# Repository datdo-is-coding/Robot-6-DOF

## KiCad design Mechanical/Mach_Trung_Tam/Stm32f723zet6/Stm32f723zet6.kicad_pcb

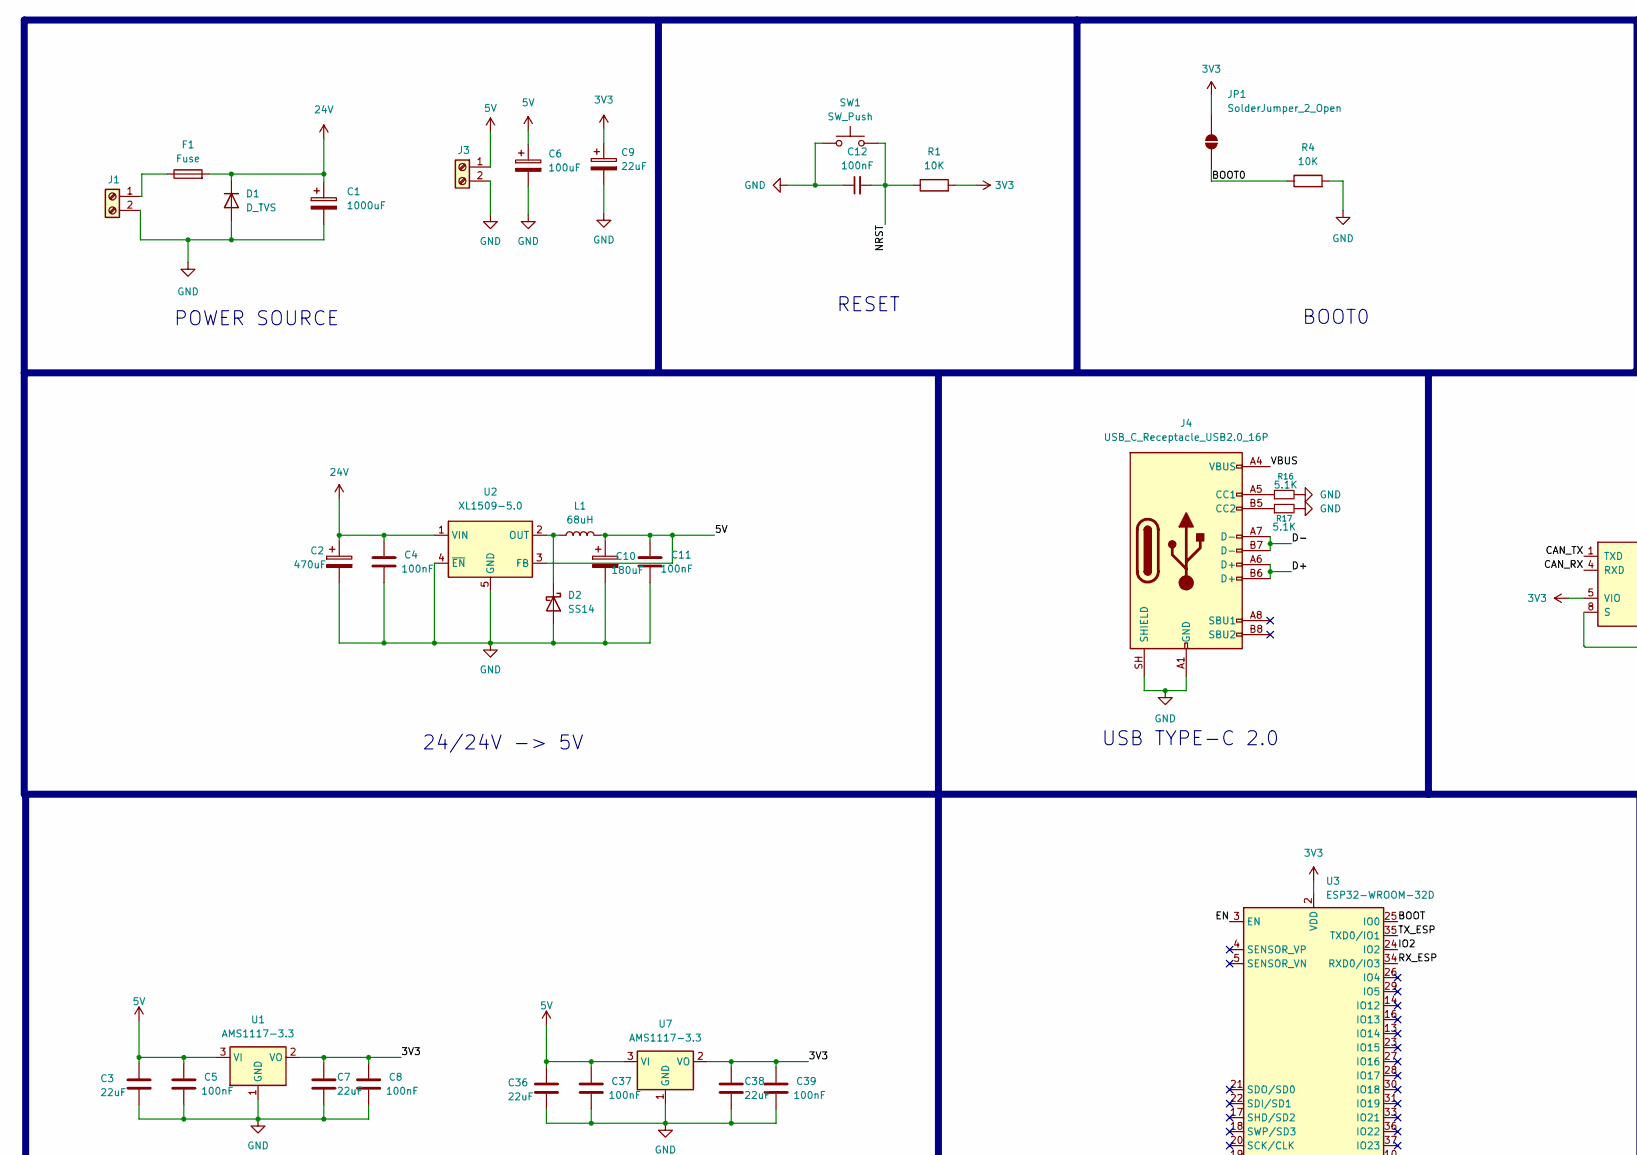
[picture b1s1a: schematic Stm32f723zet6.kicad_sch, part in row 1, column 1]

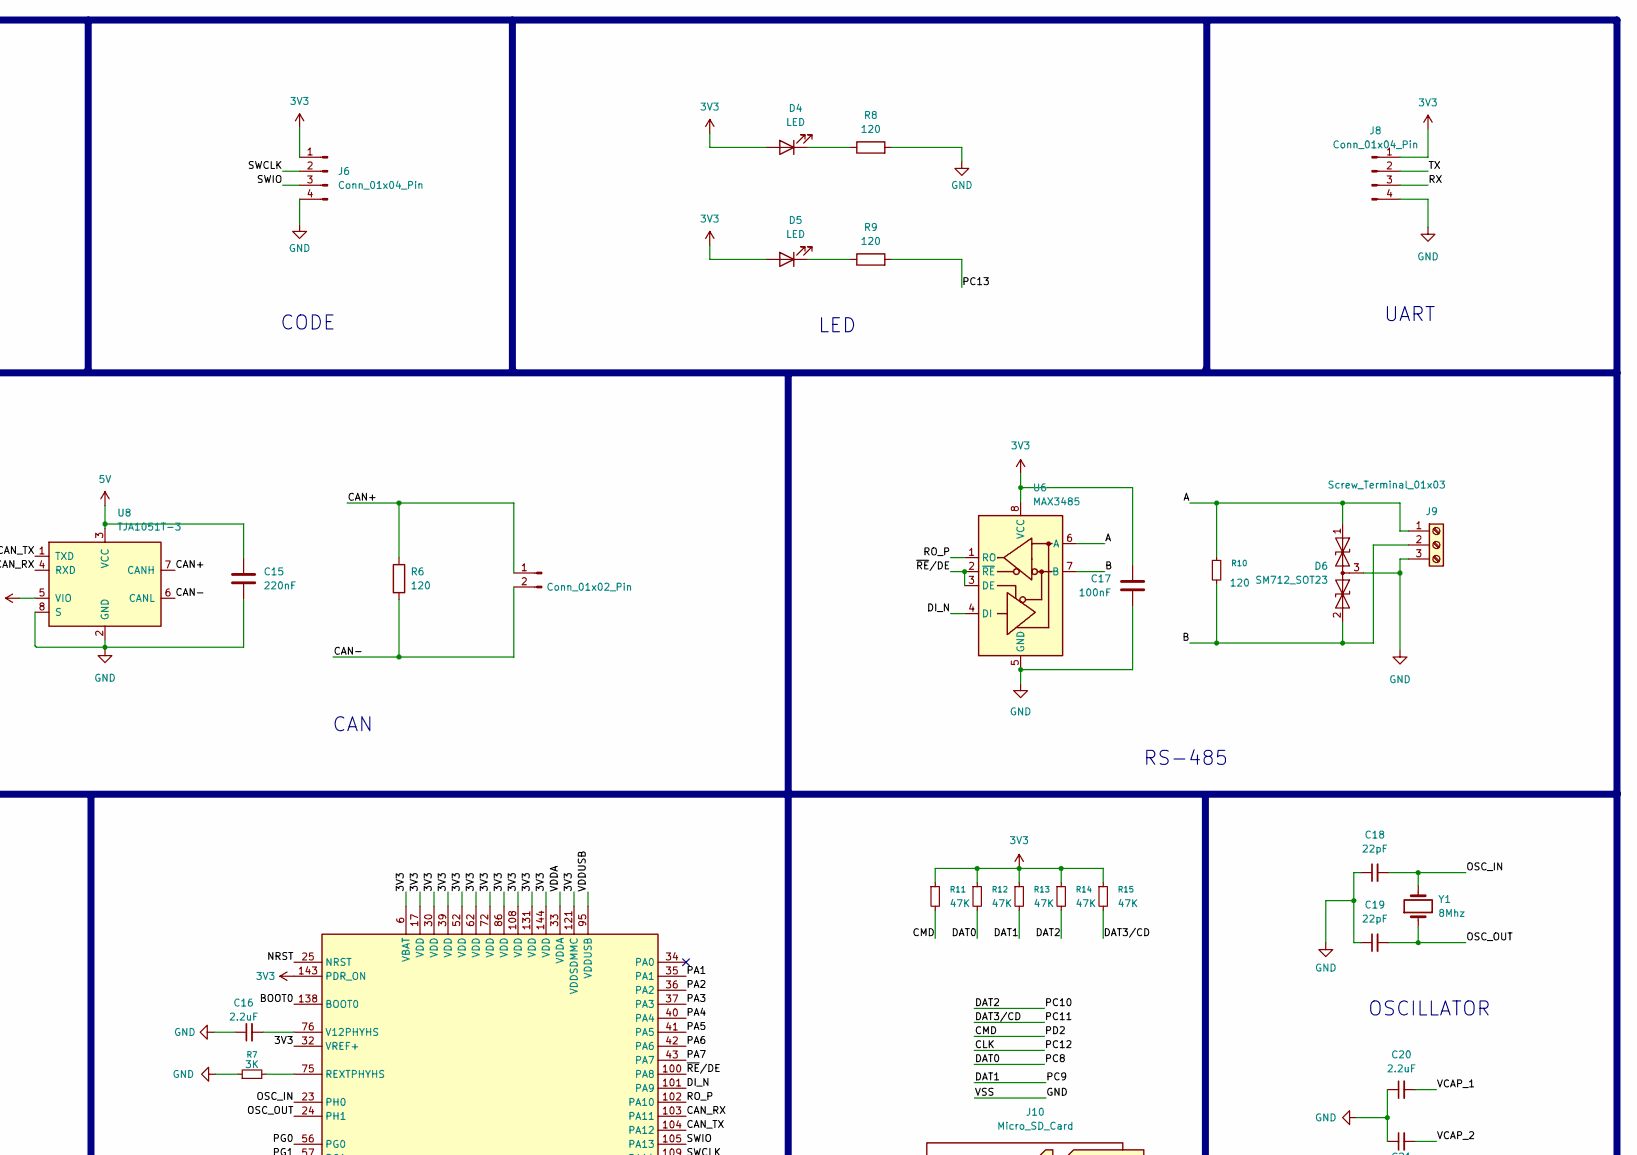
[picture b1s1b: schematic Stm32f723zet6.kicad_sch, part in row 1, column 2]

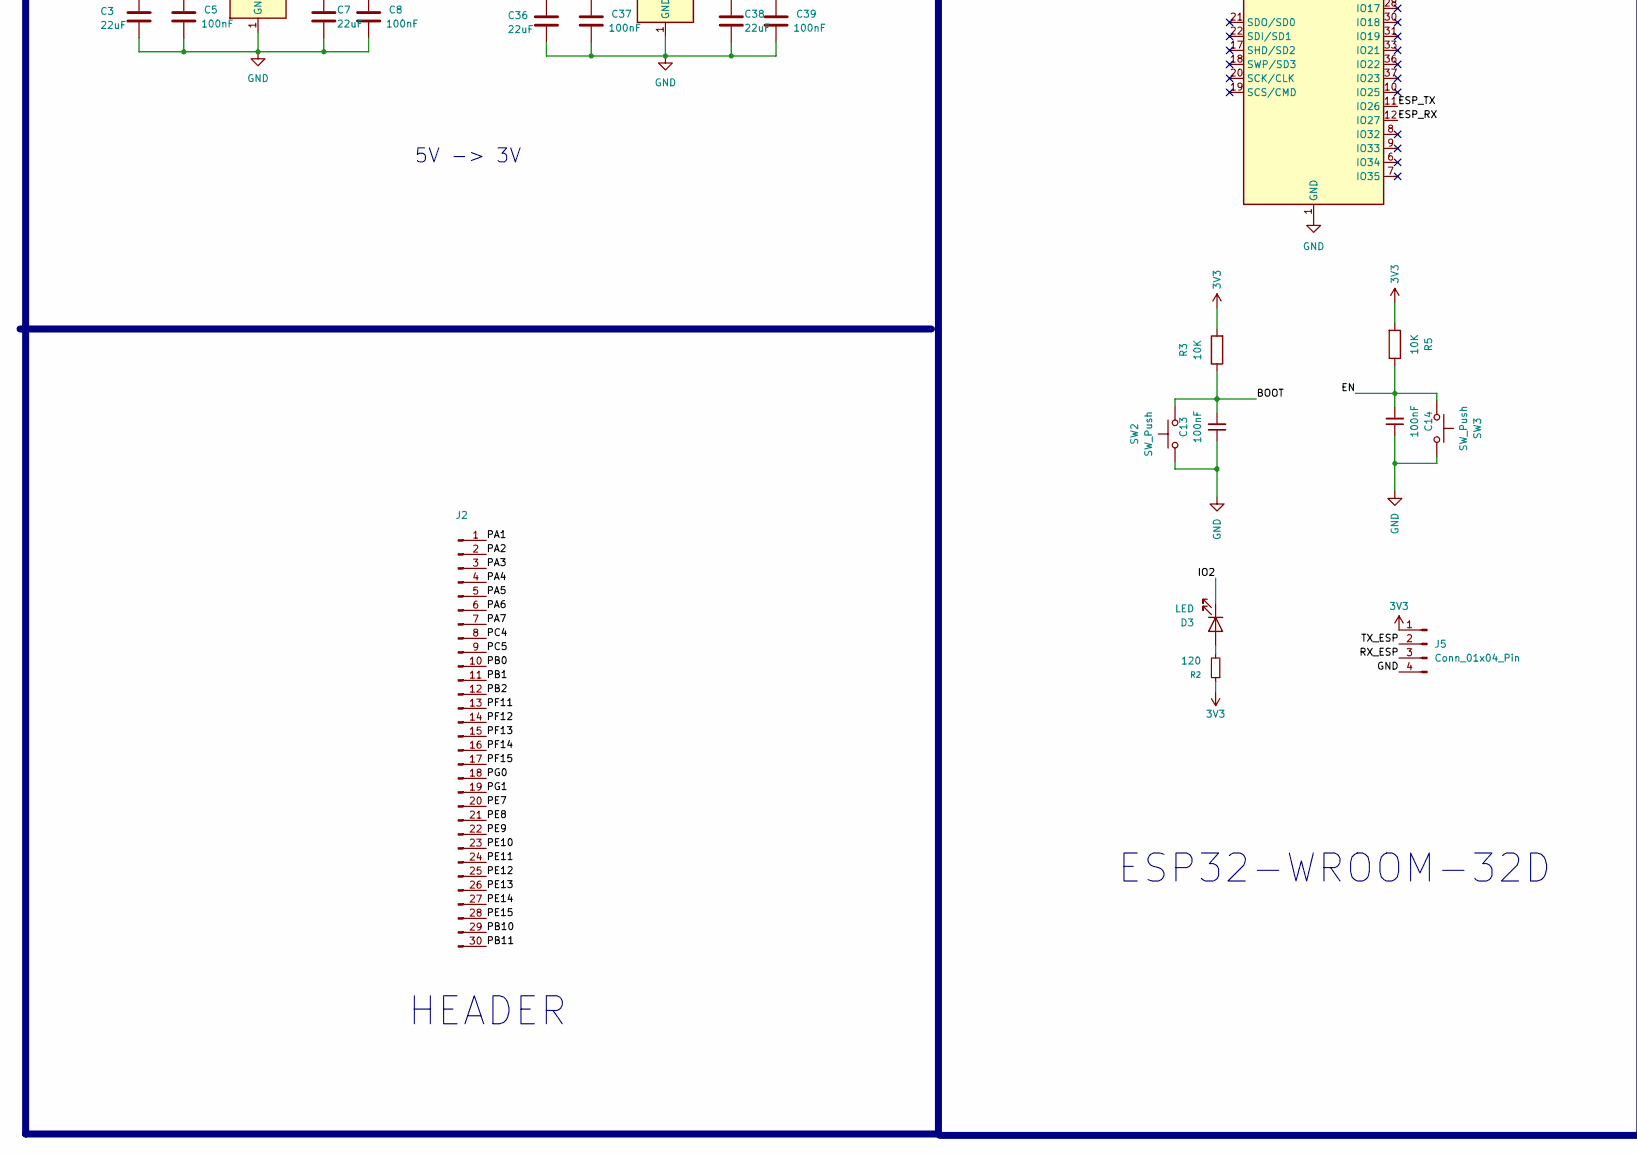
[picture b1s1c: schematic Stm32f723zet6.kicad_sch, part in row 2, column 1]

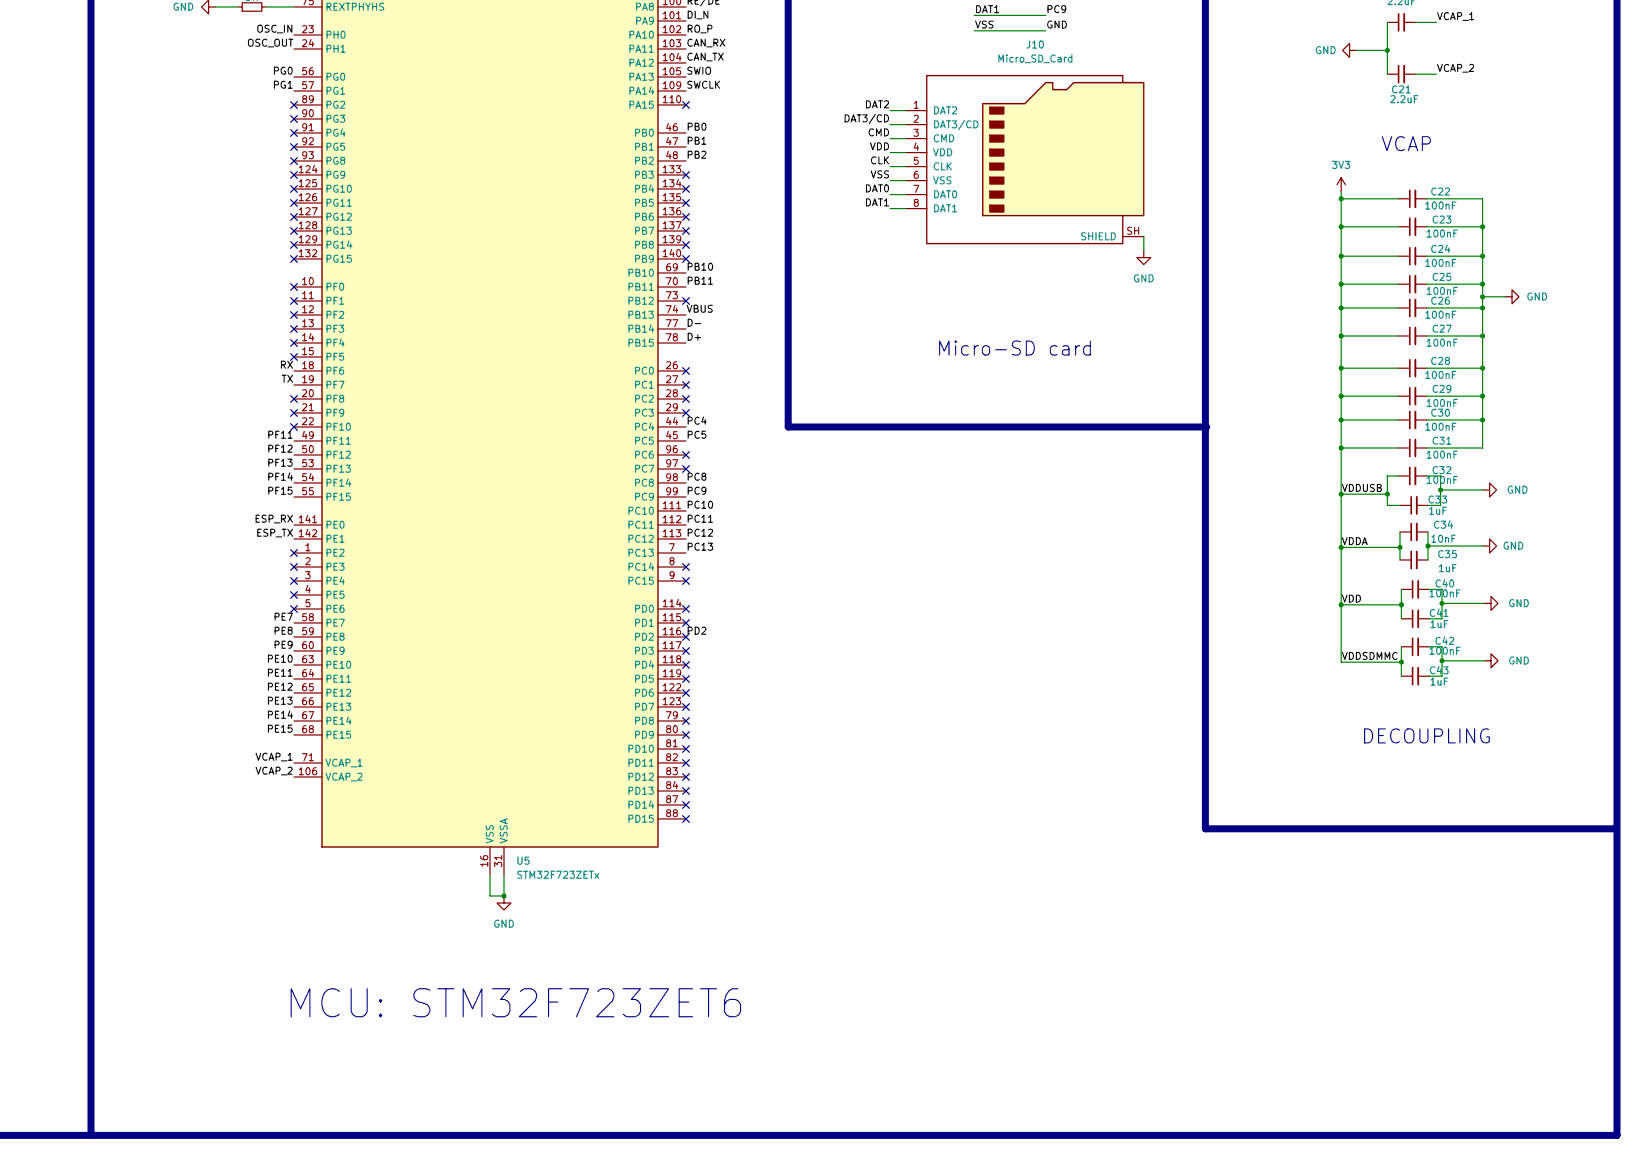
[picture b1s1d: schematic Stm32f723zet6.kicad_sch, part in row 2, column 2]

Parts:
C1: 1000uF; CP_Elec_10x10.5
C2: 470uF; CP_Elec_8x10.5
C3, C7, C36, C38: 22uF; C_0805_2012Metric_Pad1.18x1.45mm_HandSolder
C4, C5, C8, C11, C12, C13, C14, C17, C22, C23, C24, C25, C26, C27, C28, C29, C30, C31, C32, C37, C39, C40, C42: 100nF; C_0805_2012Metric_Pad1.18x1.45mm_HandSolder
C6: 100uF; CP_Elec_6.3x5.4
C9: 22uF; CP_Elec_4x5.4
C10: 180uF; CP_Elec_8x10
C15: 220nF; C_0805_2012Metric_Pad1.18x1.45mm_HandSolder
C16, C20, C21: 2.2uF; C_0805_2012Metric_Pad1.18x1.45mm_HandSolder
C18, C19: 22pF; C_0805_2012Metric_Pad1.18x1.45mm_HandSolder
C33, C35, C41, C43: 1uF; C_0805_2012Metric_Pad1.18x1.45mm_HandSolder
C34: 10nF; C_0805_2012Metric_Pad1.18x1.45mm_HandSolder
D1: D_TVS; D_SMB_Handsoldering
D2: SS14; D_SMA
D3, D4, D5: LED; LED_0805_2012Metric_Pad1.15x1.40mm_HandSolder
D6: SM712_SOT23; SOT-23
F1: Fuse; Fuse_1206_3216Metric
J1: Screw_Terminal_01x02; TerminalBlock_Phoenix_MKDS-1,5-2-5.08_1x02_P5.08mm_Horizont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
J2: Conn_01x30_Pin; PinHeader_1x30_P2.54mm_Vertical
J3: Screw_Terminal_01x02; TerminalBlock_Phoenix_PT-1,5-2-3.5-H_1x02_P3.50mm_Horizontal
J4: USB_C_Receptacle_USB2.0_16P; USB_C_Receptacle_GCT_USB4105-xx-A_16P_TopMnt_Horizontal
J5, J6, J8: Conn_01x04_Pin; PinHeader_1x04_P2.54mm_Vertical
J7: Conn_01x02_Pin; PinHeader_1x02_P2.54mm_Vertical
J9: Screw_Terminal_01x03; TerminalBlock_Phoenix_PT-1,5-3-3.5-H_1x03_P3.50mm_Horizontal
J10: Micro_SD_Card; microSD_HC_Molex_47219-2001
JP1: SolderJumper_2_Open; SolderJumper-2_P1.3mm_Open_Pad1.0x1.5mm
L1: 68uH; L_0805_2012Metric_Pad1.05x1.20mm_HandSolder
R1, R3, R4, R5: 10K; R_0805_2012Metric_Pad1.20x1.40mm_HandSolder
R2, R6, R8, R9, R10: 120; R_0805_2012Metric_Pad1.20x1.40mm_HandSolder
R7: 3K; R_0805_2012Metric_Pad1.20x1.40mm_HandSolder
R11, R12, R13, R14, R15: 47K; R_0805_2012Metric_Pad1.20x1.40mm_HandSolder
R16, R17: 5.1K; R_0805_2012Metric_Pad1.20x1.40mm_HandSolder
SW1, SW2, SW3: SW_Push; SW_Tactile_SPST_NO_Straight_CK_PTS636Sx25SMTRLFS
U1, U7: AMS1117-3.3; SOT-223-3_TabPin2
U2: XL1509-5.0; SOIC-8_3.9x4.9mm_P1.27mm
U3: ESP32-WROOM-32D
U5: STM32F723ZETx; LQFP-144_20x20mm_P0.5mm
U6: MAX3485; SOIC-8_3.9x4.9mm_P1.27mm
U8: TJA1051T-3; SOIC-8_3.9x4.9mm_P1.27mm
Y1: 8Mhz; Crystal_SMD_5032-2Pin_5.0x3.2mm_HandSoldering

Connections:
3V3: C7.1, C8.1, C9.1, C17.2, C22.1, C23.1, C24.1, C25.1, C26.1, C27.1, C28.1, C29.1, C30.1, C31.1, C32.1, C33.1, C34.1, C35.1, C38.1, C39.1, C40.1, C41.1, C42.1, C43.1, D4.2 (A), D5.2 (A), J5.1, J6.1, J8.1, J10.4 (VDD), JP1.2 (B), R1.2, R2.1, R3.2, R5.2, R11.1, R12.1, R13.1, R14.1, R15.1, U1.2 (VO), U3.2 (VDD), U5.6 (VBAT), U5.17 (VDD), U5.30 (VDD), U5.32 (VREF+), U5.33 (VDDA), U5.39 (VDD), U5.52 (VDD), U5.62 (VDD), U5.72 (VDD), U5.86 (VDD), U5.95 (VDDUSB), U5.108 (VDD), U5.121 (VDDSDMMC), U5.131 (VDD), U5.143 (PDR_ON), U5.144 (VDD), U6.8 (VCC), U7.2 (VO), U8.5 (VIO)
5V: C3.1, C5.1, C6.1, C10.1, C11.1, C15.1, C36.1, C37.1, J3.1, L1.2, U1.3 (VI), U2.3 (FB), U7.3 (VI), U8.3 (VCC)
24V: C1.1, C2.1, C4.1, D1.1 (K), F1.2, U2.1 (VIN)
/A: D6.1 (A1), J9.1, R10.1, U6.6 (A)
/B: D6.2 (A2), J9.2, R10.2, U6.7 (B)
/BOOT: C13.2, R3.1, SW2.2, U3.25 (IO0)
/BOOT0: JP1.1 (A), R4.1, U5.138 (BOOT0)
/CAN+: J7.1, R6.1, U8.7 (CANH)
/CAN-: J7.2, R6.2, U8.6 (CANL)
/CAN_RX: U5.103 (PA11), U8.4 (RXD)
/CAN_TX: U5.104 (PA12), U8.1 (TXD)
/CLK: J10.5 (CLK), U5.113 (PC12)
/CMD: J10.3 (CMD), R11.2, U5.116 (PD2)
/D+: J4.A6 (D+), J4.B6 (D+), U5.78 (PB15)
/D-: J4.A7 (D-), J4.B7 (D-), U5.77 (PB14)
/DAT0: J10.7 (DAT0), R12.2, U5.98 (PC8)
/DAT1: J10.8 (DAT1), R13.2, U5.99 (PC9)
/DAT2: J10.1 (DAT2), R14.2, U5.111 (PC10)
/DAT3/CD: J10.2 (DAT3/CD), R15.2, U5.112 (PC11)
/DI_N: U5.101 (PA9), U6.4 (DI)
/EN: C14.2, R5.1, SW3.2, U3.3 (EN)
/ESP_RX: U3.12 (IO27), U5.141 (PE0)
/ESP_TX: U3.11 (IO26), U5.142 (PE1)
/IO2: D3.1 (K), U3.24 (IO2)
/NRST: C12.2, R1.1, SW1.2, U5.25 (NRST)
/OSC_IN: C18.2, U5.23 (PH0), Y1.2
/OSC_OUT: C19.2, U5.24 (PH1), Y1.1
/PA1: J2.1, U5.35 (PA1)
/PA2: J2.2, U5.36 (PA2)
/PA3: J2.3, U5.37 (PA3)
/PA4: J2.4, U5.40 (PA4)
/PA5: J2.5, U5.41 (PA5)
/PA6: J2.6, U5.42 (PA6)
/PA7: J2.7, U5.43 (PA7)
/PB0: J2.10, U5.46 (PB0)
/PB1: J2.11, U5.47 (PB1)
/PB2: J2.12, U5.48 (PB2)
/PB10: J2.29, U5.69 (PB10)
/PB11: J2.30, U5.70 (PB11)
/PC4: J2.8, U5.44 (PC4)
/PC5: J2.9, U5.45 (PC5)
/PC13: R9.2, U5.7 (PC13)
/PE7: J2.20, U5.58 (PE7)
/PE8: J2.21, U5.59 (PE8)
/PE9: J2.22, U5.60 (PE9)
/PE10: J2.23, U5.63 (PE10)
/PE11: J2.24, U5.64 (PE11)
/PE12: J2.25, U5.65 (PE12)
/PE13: J2.26, U5.66 (PE13)
/PE14: J2.27, U5.67 (PE14)
/PE15: J2.28, U5.68 (PE15)
/PF11: J2.13, U5.49 (PF11)
/PF12: J2.14, U5.50 (PF12)
/PF13: J2.15, U5.53 (PF13)
/PF14: J2.16, U5.54 (PF14)
/PF15: J2.17, U5.55 (PF15)
/PG0: J2.18, U5.56 (PG0)
/PG1: J2.19, U5.57 (PG1)
/RO_P: U5.102 (PA10), U6.1 (RO)
/RX: J8.3, U5.18 (PF6)
/RX_ESP: J5.3, U3.34 (RXD0/IO3)
/SWCLK: J6.2, U5.109 (PA14)
/SWIO: J6.3, U5.105 (PA13)
/TX: J8.2, U5.19 (PF7)
/TX_ESP: J5.2, U3.35 (TXD0/IO1)
/VBUS: J4.A4 (VBUS), J4.A9 (VBUS), J4.B4 (VBUS), J4.B9 (VBUS), U5.74 (PB13)
/VCAP_1: C20.2, U5.71 (VCAP_1)
/VCAP_2: C21.2, U5.106 (VCAP_2)
/~RE/DE: U5.100 (PA8), U6.2 (~RE), U6.3 (DE)
GND: C1.2, C2.2, C3.2, C4.2, C5.2, C6.2, C7.2, C8.2, C9.2, C10.2, C11.2, C12.1, C13.1, C14.1, C15.2, C16.1, C17.1, C18.1, C19.1, C20.1, C21.1, C22.2, C23.2, C24.2, C25.2, C26.2, C27.2, C28.2, C29.2, C30.2, C31.2, C32.2, C33.2, C34.2, C35.2, C36.2, C37.2, C38.2, C39.2, C40.2, C41.2, C42.2, C43.2, D1.2 (A), D2.2 (A), D6.3 (common), J1.2, J3.2, J4.A1 (GND), J4.A12 (GND), J4.B1 (GND), J4.B12 (GND), J4.SH (SHIELD), J5.4, J6.4, J8.4, J9.3, J10.6 (VSS), J10.SH (SHIELD), R4.2, R7.1, R8.2, R16.2, R17.2, SW1.1, SW2.1, SW3.1, U1.1 (GND), U2.4 (~EN), U2.5 (GND), U2.6 (GND), U2.7 (GND), U2.8 (GND), U3.1 (GND), U3.15 (GND), U3.38 (GND), U3.39 (GND), U5.16 (VSS), U5.31 (VSSA), U5.38 (VSS), U5.51 (VSS), U5.61 (VSS), U5.85 (VSS), U5.94 (VSS), U5.107 (VSS), U5.120 (VSS), U5.130 (VSS), U6.5 (GND), U7.1 (GND), U8.2 (GND), U8.8 (S)
unnamed: D2.1 (K), L1.1, U2.2 (OUT)
unnamed: D3.2 (A), R2.2
unnamed: D4.1 (K), R8.1
unnamed: D5.1 (K), R9.1
unnamed: F1.1, J1.1
unnamed: J4.A5 (CC1), R16.1
unnamed: J4.B5 (CC2), R17.1
unnamed: R7.2, U5.75 (REXTPHYHS)
unnamed: C16.2, U5.76 (V12PHYHS)

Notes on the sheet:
5V -> 3V
VCAP
CODE
HEADER
POWER SOURCE
RESET
BOOT0
CAN
USB TYPE-C 2.0
Micro-SD card
MCU: STM32F723ZET6
24/24V -> 5V
LED
UART
OSCILLATOR
DECOUPLING
ESP32-WROOM-32D
RS-485

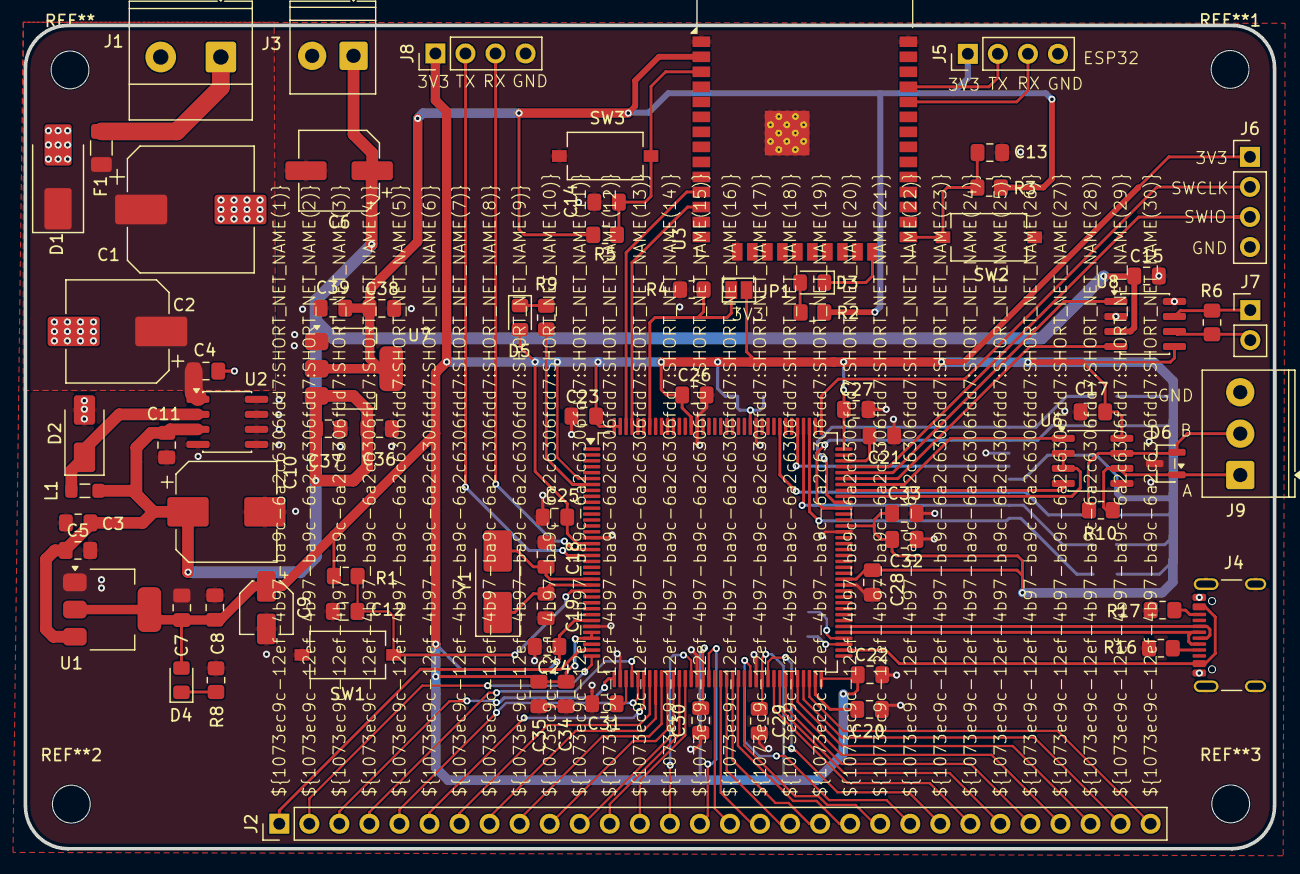
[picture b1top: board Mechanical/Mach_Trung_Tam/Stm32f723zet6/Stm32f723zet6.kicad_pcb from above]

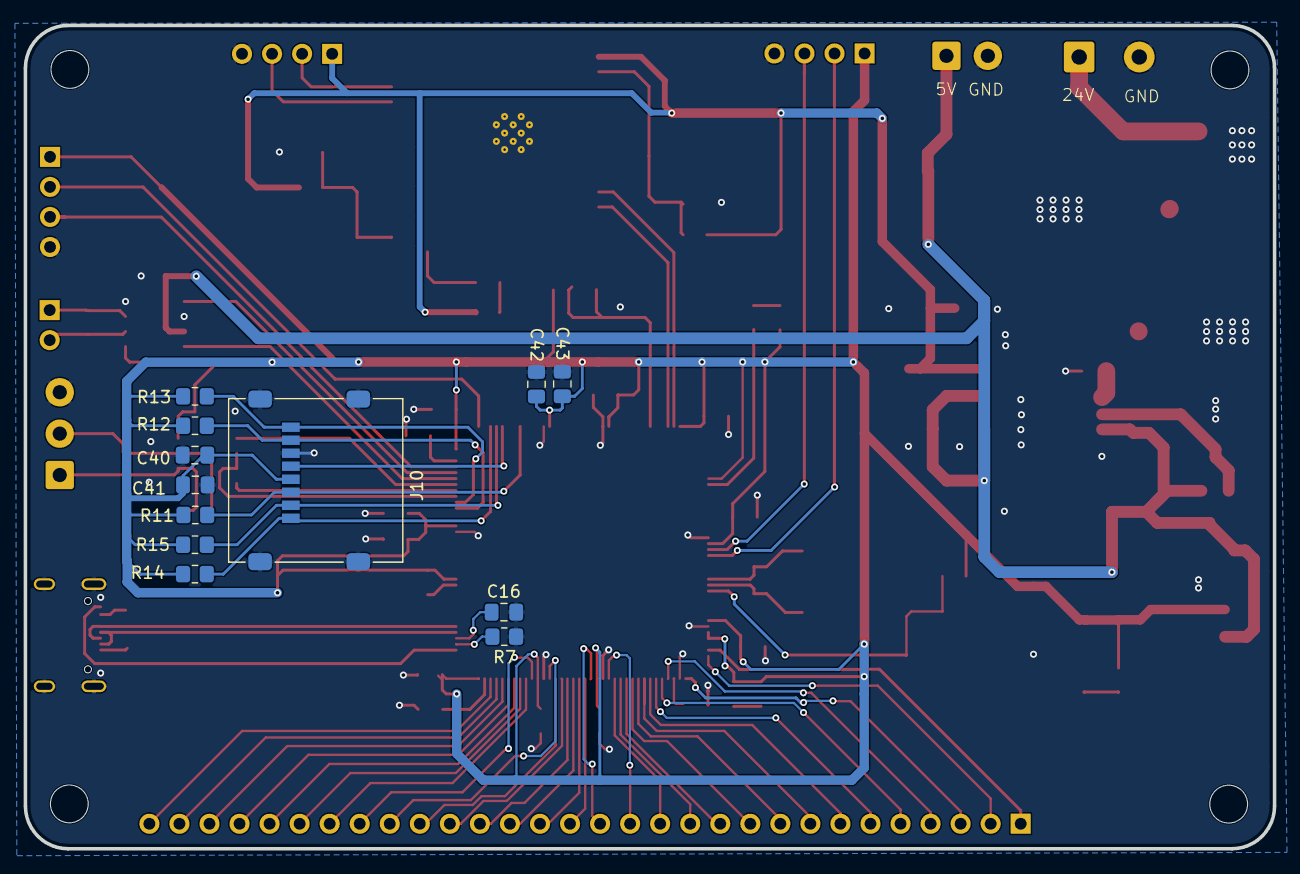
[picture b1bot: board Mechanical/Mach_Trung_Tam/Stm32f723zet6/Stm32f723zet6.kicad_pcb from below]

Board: 2 copper layers, 105.6 x 69.6 mm, 90 parts (12 on the bottom side), 79 nets.
